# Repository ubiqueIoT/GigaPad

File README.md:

# GigaPad: A Wireless Macropad based on ZMK

The firmware source repository: [ZMK Configuration](https://github.com/ubiqueIoT/zmk-config-gigapad) 

A full write up about the configuration: [Gigapad write up](https://ubiqueiot.com/posts/xiao-nrf52840-zmk)

</br>

| Part      | Quantity Used |
| ----------- | ----------- |
| [Seeed Studio XIAO nRF52840](https://amzn.to/42SCjPg) | 1 |
| [EC11 Rotary Encoder](https://amzn.to/3UNgU8d)| 1 |
| [Rotary Encoder Knob](https://amzn.to/3uBRqQz) | 1 |
| [Cherry MX Switches](https://amzn.to/3T9t7Tl) | 3 |
| [Keycaps](https://amzn.to/49hurct) | 3 |
| [Self tapping screws](https://www.mcmaster.com/catalog/130/3420/90380A344) | 4 |
| [Rubber feet](https://amzn.to/3T9w9XM) | 4 |

</br>
The battery should be soldered to the pads on the bottom of the XIAO module BEFORE mounting it to the PCB. Once the module is soldered in place on the PCB, you will **not** be able to access the battery pads again. Be careful with bare battery leads!
</br>

</br>

</br>

</br>

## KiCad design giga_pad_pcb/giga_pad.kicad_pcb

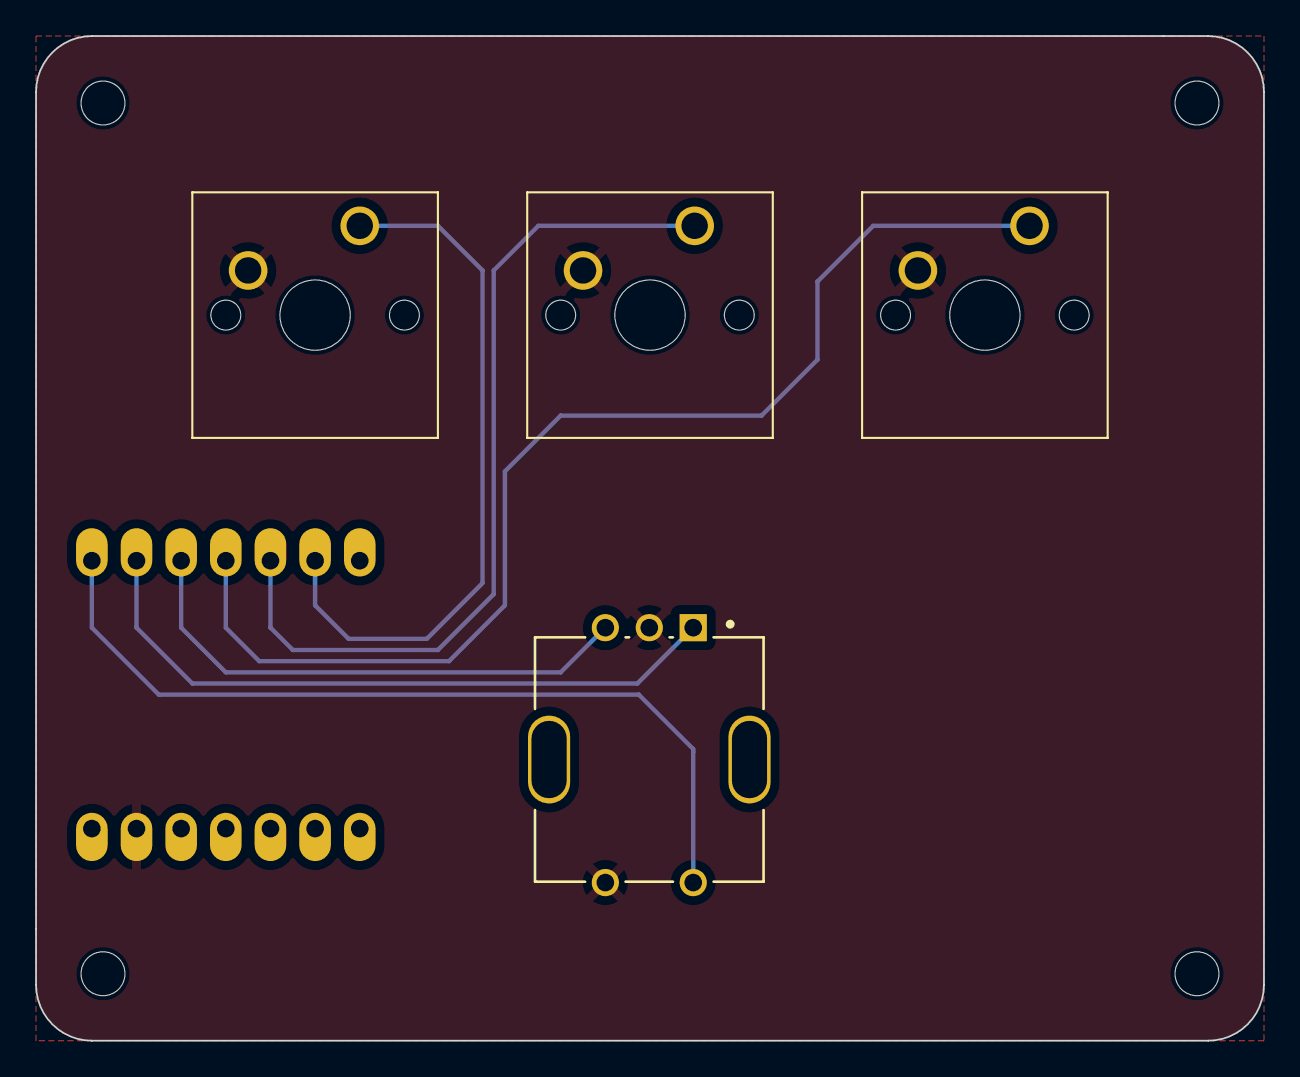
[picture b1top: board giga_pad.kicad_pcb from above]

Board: 2 copper layers, 69.8 x 57.2 mm, 9 parts (1 on the bottom side), 7 nets.

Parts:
H1, H2, H3, H4: MountingHole; MountingHole_2.5mm
SW1: RotaryEncoder_Switch; Bourns-PEC11R-4220F-S0024-0-0-0
SW2, SW3, SW4: SW_Push; SW_Cherry_MX_1.00u_PCB
U1: SeeeduinoXIAO; xiao-tht

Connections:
GND: SW1.2, SW1.C, SW2.2, SW3.2, SW4.2, U1.13 (GND)
ROT_A: SW1.A, U1.2 (PA4_A1_D1)
ROT_B: SW1.B, U1.3 (PA10_A2_D2)
ROT_SW: SW1.1, U1.1 (PA02_A0_D0)
SW_2: SW2.1, U1.4 (PA11_A3_D3)
SW_3: SW3.1, U1.5 (PA8_A4_D4_SDA)
SW_4: SW4.1, U1.6 (PA9_A5_D5_SCL)

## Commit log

2024-02-22 read me
2024-03-06 Show battery
